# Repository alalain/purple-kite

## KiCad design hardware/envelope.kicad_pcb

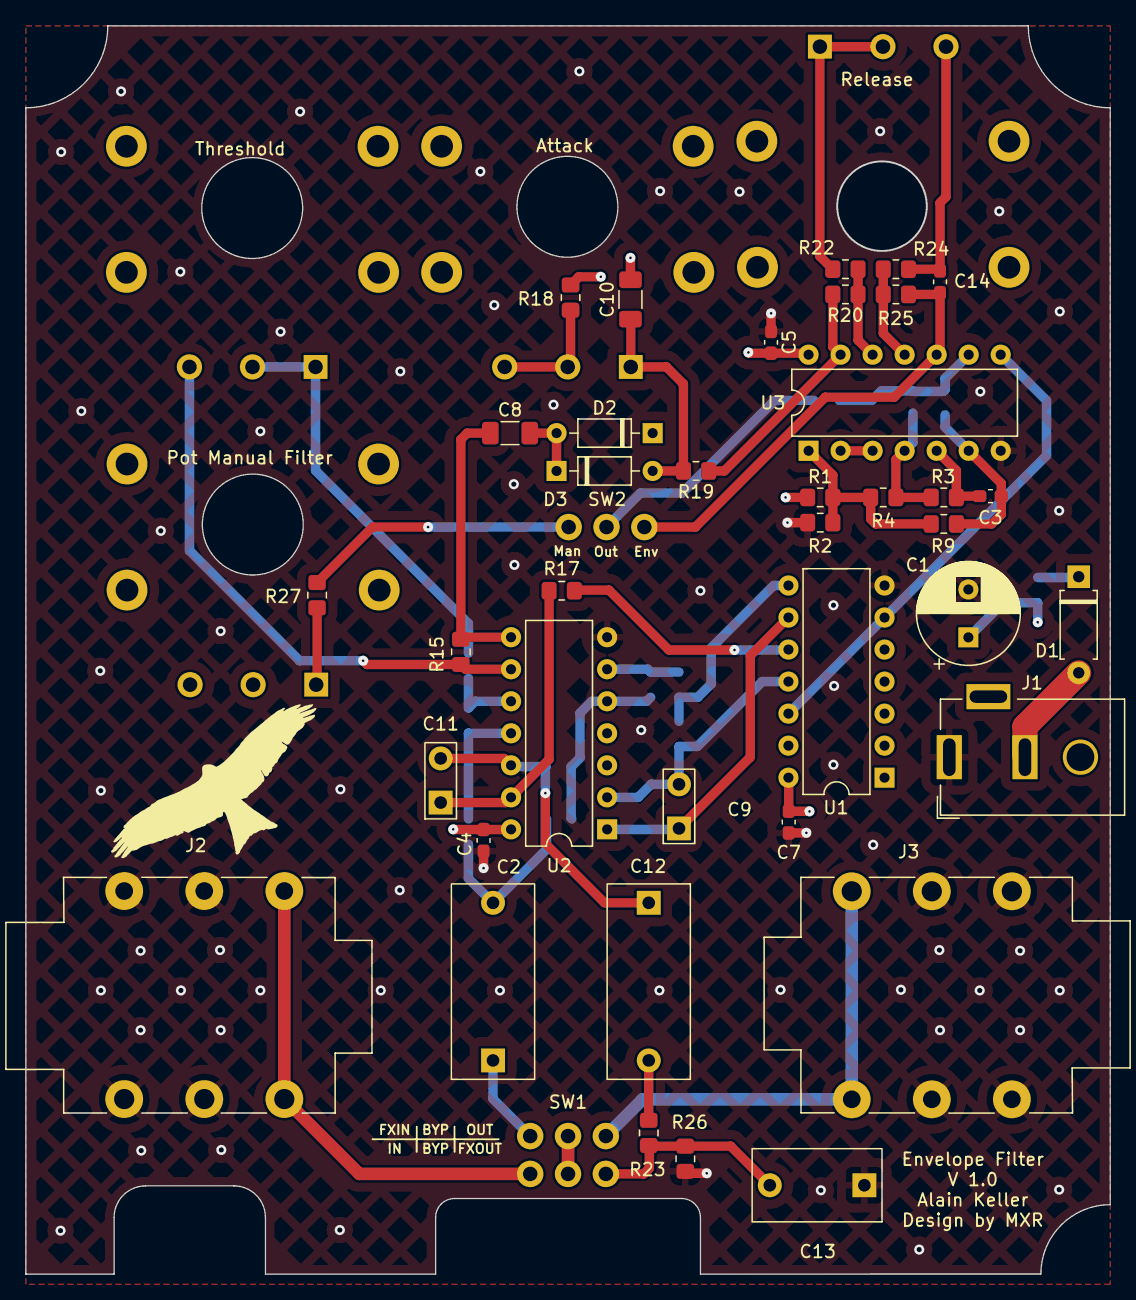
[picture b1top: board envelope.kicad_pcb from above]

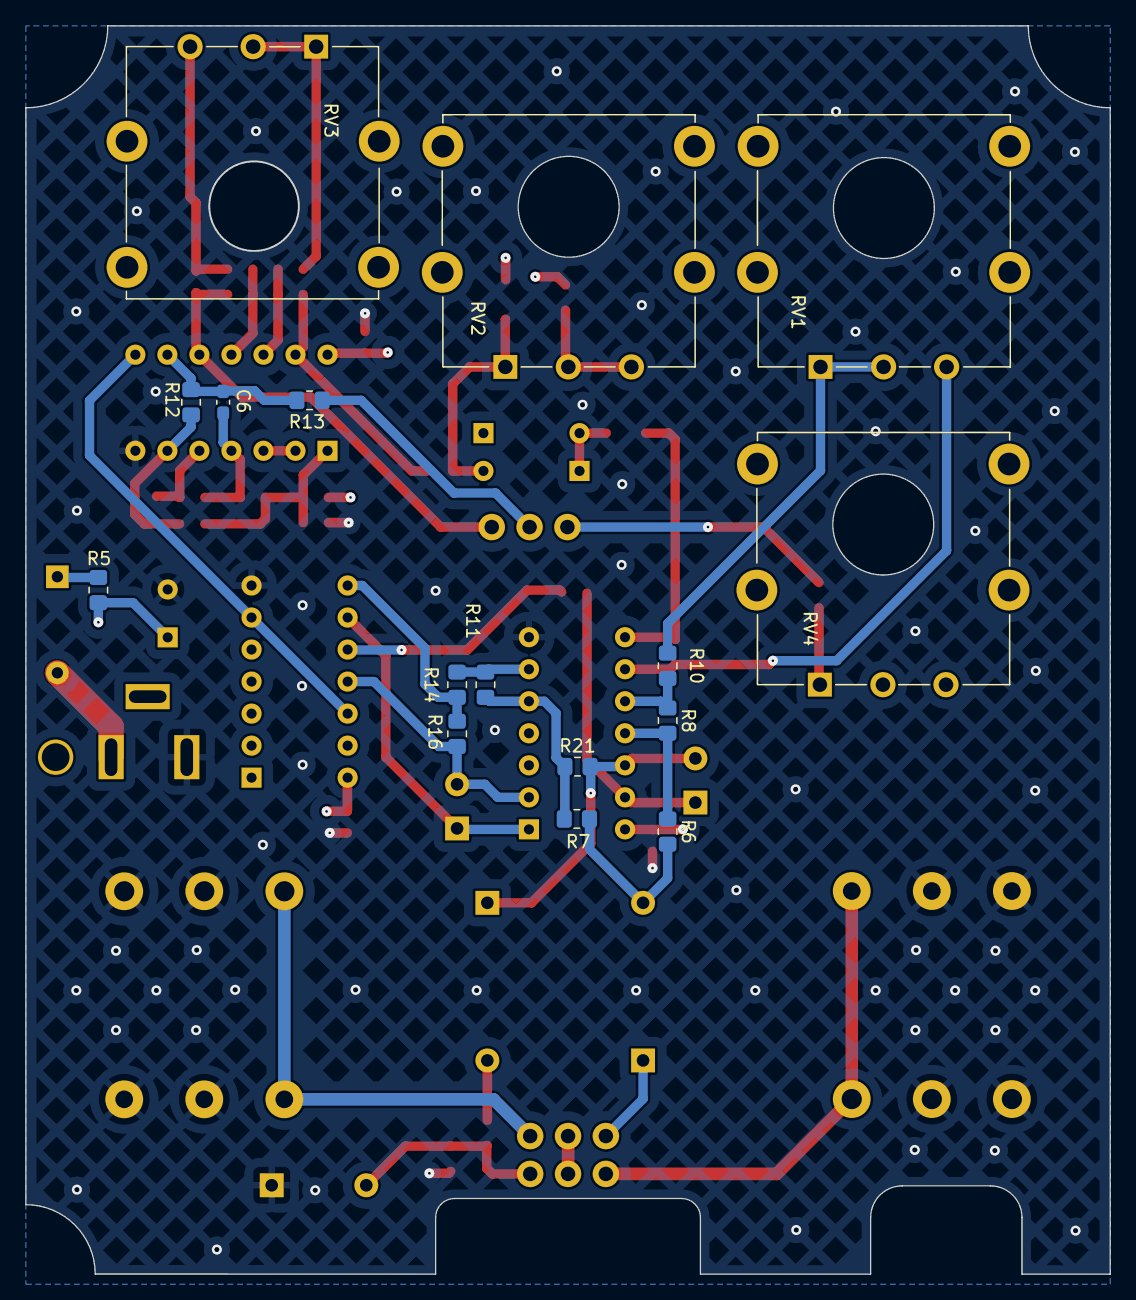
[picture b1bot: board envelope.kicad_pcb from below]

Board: 4 copper layers, 86.0 x 99.0 mm, 56 parts (16 on the bottom side), 43 nets.

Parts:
C1: 47u; CP_Radial_D8.0mm_P3.80mm
C2, C12: 0.05u; cap_12.5mm-l15.5-w6.6mm
C3: 100p; C_0603_1608Metric_Pad1.08x0.95mm_HandSolder
C4, C5, C7: 100n; C_0603_1608Metric_Pad1.08x0.95mm_HandSolder
C6: 10p; C_0603_1608Metric_Pad1.08x0.95mm_HandSolder
C8, C10: 0.05u; C_1206_3216Metric_Pad1.33x1.80mm_HandSolder
C9, C11: 1n; cap_3.5mm-l5-w2.5mm_copy
C13: 0.1u; cap_7.5mm-l10.3-w5.8mm
C14: 0.1u; C_0603_1608Metric_Pad1.08x0.95mm_HandSolder
D1: D_Schottky; D_A-405_P7.62mm_Horizontal
D2, D3: 1N914; D_DO-35_SOD27_P7.62mm_Horizontal
J1: Barrel_Jack_Switch_MountingPin; BarrelJack_CUI_PJ-102AH_CUIDevices
J2, J3: AudioJack3_Switch; newJack
R1: 62k; R_0805_2012Metric_Pad1.20x1.40mm_HandSolder
R2, R3, R4: 100k; R_0805_2012Metric_Pad1.20x1.40mm_HandSolder
R5: 3k; R_0805_2012Metric_Pad1.20x1.40mm_HandSolder
R6: 1M; R_0805_2012Metric_Pad1.20x1.40mm_HandSolder
R7, R16, R21, R26: 200k; R_0805_2012Metric_Pad1.20x1.40mm_HandSolder
R8: 5.1M; R_0805_2012Metric_Pad1.20x1.40mm_HandSolder
R9, R12, R13, R14, R17: 47k; R_0805_2012Metric_Pad1.20x1.40mm_HandSolder
R10, R22, R27: 10k; R_0805_2012Metric_Pad1.20x1.40mm_HandSolder
R11: 240k; R_0805_2012Metric_Pad1.20x1.40mm_HandSolder
R15: 470k; R_0805_2012Metric_Pad1.20x1.40mm_HandSolder
R18: 700k; R_0805_2012Metric_Pad1.20x1.40mm_HandSolder
R19, R25: 22M; R_0805_2012Metric_Pad1.20x1.40mm_HandSolder
R20, R24: 10M; R_0805_2012Metric_Pad1.20x1.40mm_HandSolder
R23: 3k6; R_0805_2012Metric_Pad1.20x1.40mm_HandSolder
RV1, RV2, RV3: 500k; alpha_poti
RV4: 100k; alpha_poti
SW1: SW_DPDT_x2; tht_ext_footswitch
SW2: SW_SPDT; tht_ext_toggle_switch
U1: 4066; DIP-14_W7.62mm
U2, U3: 4069; DIP-14_W7.62mm

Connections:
GND: C1.2, C4.1, C5.1, C7.1, C13.1, J1.1, J2.R, J2.RN, J2.S, J2.SN, J3.R, J3.RN, J3.S, J3.SN, R2.2, R26.1, U1.7 (VSS), U2.7 (VSS), U3.7 (VSS)
unnamed: C2.1, SW1.3 (C)
unnamed: C2.2, R6.2, R7.1
unnamed: C3.1, R3.1, U3.5
unnamed: C3.2, R9.2, R12.1, U3.6
unnamed: C6.1, R3.2, R4.2, U3.4
unnamed: C6.2, R12.2, R13.2, U3.9
unnamed: C8.1, R15.1, U2.8
unnamed: C8.2, D2.2 (A), D3.1 (K)
unnamed: C9.1, U1.9, U2.1
unnamed: C9.2, R16.2, U1.11, U2.2
unnamed: C10.1, D3.2 (A), R19.2, RV2.1
unnamed: C11.1, R17.2, U2.13
unnamed: C11.2, C12.1, R21.2, U2.12
unnamed: C12.2, R23.1
unnamed: C13.2, R23.2, R26.2, SW1.6 (C)
unnamed: C14.1, R25.1, SW2.1 (A), U3.10
unnamed: C14.2, R24.2, RV3.3
unnamed: D1.1 (K), R5.2
unnamed: D1.2 (A), J1.2
unnamed: J2.T, J2.TN, SW1.2 (B)
unnamed: J3.T, J3.TN, SW1.5 (B)
unnamed: R1.2, R2.1, R4.1, R9.1, U3.1
unnamed: R6.1, R8.2, U2.11
unnamed: R10.1, RV1.1, RV1.2
unnamed: R8.1, R10.2, U2.10
unnamed: R7.2, R11.1, R21.1, U2.5
unnamed: R11.2, R14.1, U2.6
unnamed: R13.1, SW2.2 (B)
unnamed: R14.2, R16.1, U1.8
unnamed: R15.2, RV1.3, U2.9
unnamed: R17.1, U1.10
unnamed: R18.1, RV2.2, RV2.3
unnamed: R19.1, R20.2, U3.13
unnamed: R20.1, R22.2, U3.12
unnamed: R22.1, RV3.1, RV3.2
unnamed: R24.1, R25.2, U3.11
unnamed: R27.1, RV4.1
unnamed: R27.2, SW2.3 (C)
unnamed: SW1.1 (A), SW1.4 (A)
unnamed: U3.2, U3.3
TG: U1.6, U1.12, U3.8
VS: C1.1, C4.2, C5.2, C7.2, C10.2, D2.1 (K), R1.1, R5.1, R18.2, RV4.2, RV4.3, U1.14 (VDD), U2.14 (VDD), U3.14 (VDD)

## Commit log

2024-02-01 fix power bug
2024-02-01 pre via stitch
2024-02-01 ground plane
2024-02-02 poti footprint updated
